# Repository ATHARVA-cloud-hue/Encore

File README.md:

In this video we have explained and simulated buck converter on Ltspice.Please use headphones.
https://youtu.be/Y6m0K0ljJwk

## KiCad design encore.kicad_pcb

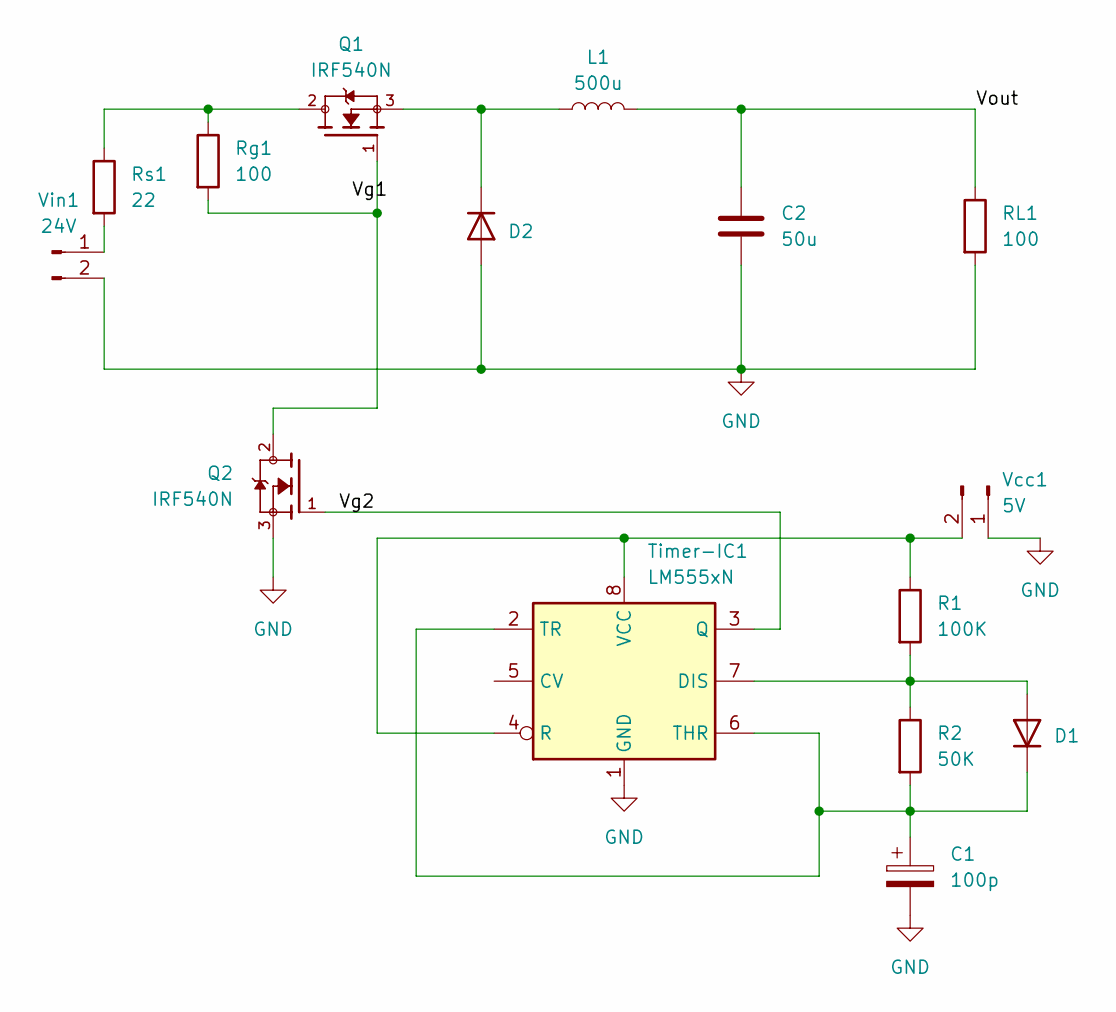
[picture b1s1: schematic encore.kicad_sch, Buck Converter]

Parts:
C1: 100p; CP_Radial_D8.0mm_P5.00mm
C2: 50u; CP_Radial_D6.3mm_P2.50mm
D1, D2: D_5W_P12.70mm_Horizontal
L1: 500u; L_Axial_L11.0mm_D4.5mm_P15.24mm_Horizontal_Fastron_MECC
Q1, Q2: IRF540N; TO254P1054X469X1930-3; PARTREV 11/3/03
R1: 100K; R_Axial_DIN0207_L6.3mm_D2.5mm_P7.62mm_Horizontal
R2: 50K; R_Axial_DIN0207_L6.3mm_D2.5mm_P7.62mm_Horizontal
RL1: 100; R_Axial_DIN0207_L6.3mm_D2.5mm_P7.62mm_Horizontal
Rg1: 100; R_Axial_DIN0207_L6.3mm_D2.5mm_P7.62mm_Horizontal
Rs1: 22; R_Axial_DIN0207_L6.3mm_D2.5mm_P7.62mm_Horizontal
Timer-IC1: LM555xN; DIP-8_W7.62mm
Vcc1: 5V; JWT_A3963_1x02_P3.96mm_Vertical
Vin1: 24V; JWT_A3963_1x02_P3.96mm_Vertical

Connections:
/Vg2: Q2.1, Timer-IC1.3 (Q)
/Vout: C2.1, L1.2, RL1.1
GND: C1.2, C2.2, D2.2 (A), Q2.3, RL1.2, Timer-IC1.1 (GND), Vcc1.1, Vin1.2
unnamed: D1.2 (A), R1.2, R2.1, Timer-IC1.7 (DIS)
unnamed: C1.1, D1.1 (K), R2.2, Timer-IC1.2 (TR), Timer-IC1.6 (THR)
unnamed: D2.1 (K), L1.1, Q1.3
unnamed: Q1.1, Q2.2, Rg1.2
unnamed: Q1.2, Rg1.1, Rs1.1
unnamed: R1.1, Timer-IC1.4 (R), Timer-IC1.8 (VCC), Vcc1.2
unnamed: Rs1.2, Vin1.1

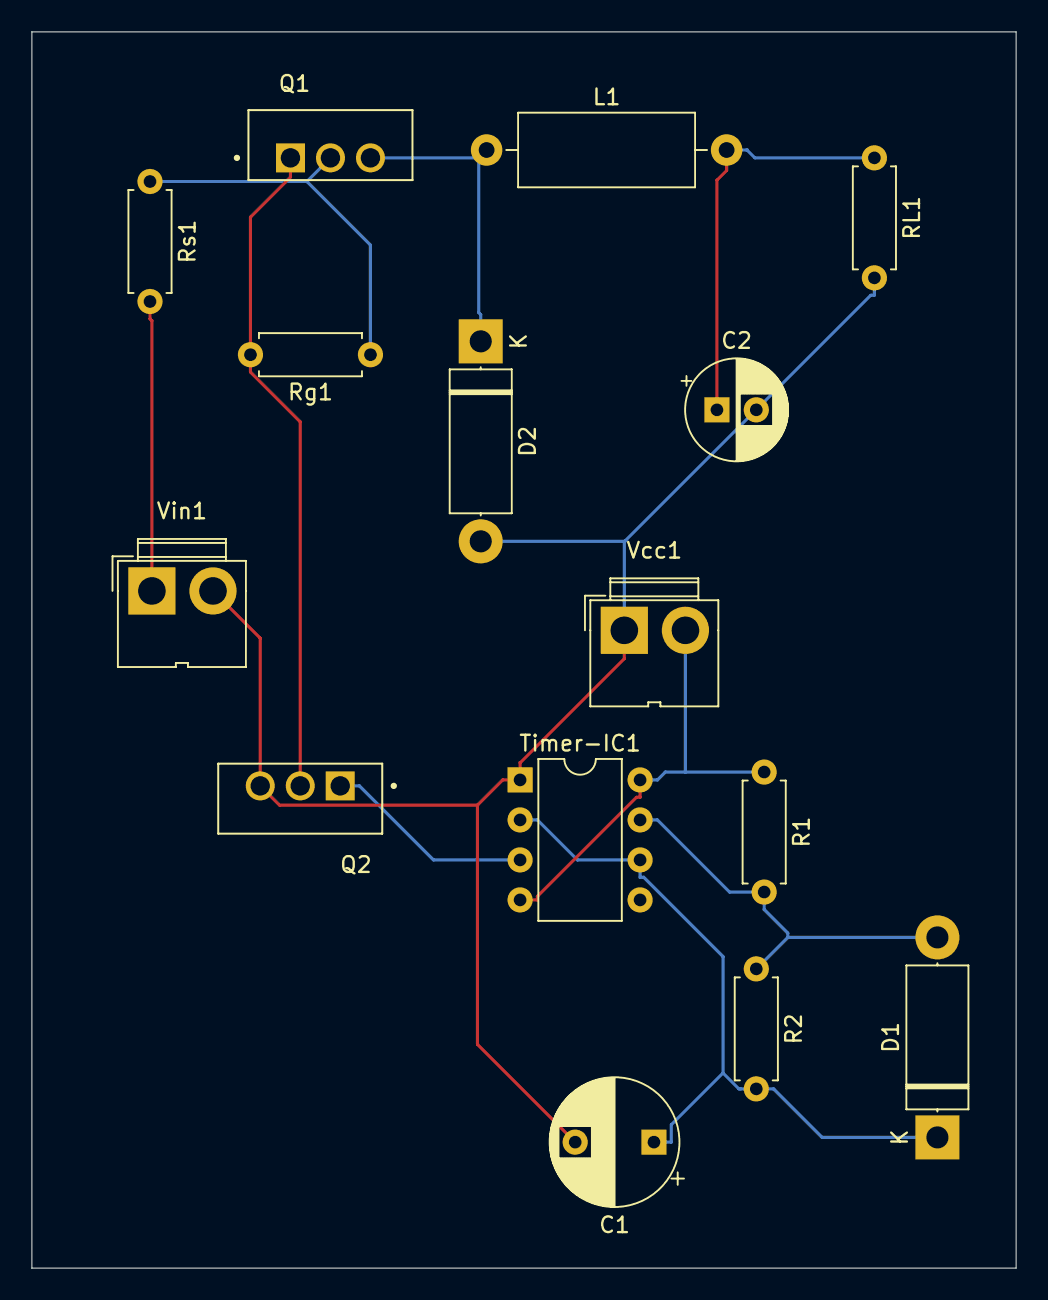
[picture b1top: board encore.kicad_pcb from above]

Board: 2 copper layers, 62.5 x 78.5 mm, 15 parts (0 on the bottom side), 10 nets.

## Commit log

2024-09-26 Create README.md
    food
